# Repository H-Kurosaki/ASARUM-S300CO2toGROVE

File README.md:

# ASARUM-S300CO2toGROVE
ELT社のCO2センサS-300をGroveコネクタに対応させる基板のデータを公開しています。

◯公開しているデータの内容

/main/GerberData

Grove化基板のガーバーデータ、FusionPCBのファイル名に準拠しています。このフォルダの内容をzipに圧縮すればそのまま発注に使えます。

/main/EagleBoard

Eagle形式のPCBデータ(GerberDataの元データ)

/main/EagleLbr

Eagle形式のライブラリS-300のフットプリント。背面のJ11,J12コネクタのみ配置してあります。おまけでK30のフットプリントも入っていますが検証していません。

/main/BOM

実装部品表

/main/ArduinoS300test

Arduino UNO R3を用いた場合のテストプログラム。I2C接続時の読み出し試験。

◯基板の仕様

S-300のI2CインターフェースをGroveケーブルで引き出すことができます。
S-300の裏側の2mmピッチコネクタを使用するので基板から簡単にセンサを着脱できる実装が行えます。
MCDL校正を行う場合は通電して起動後に10分間MCDLと書かれた部分のピンをジャンパーで短絡してください。
その他I2C以外のピンもよく使いそうなものはピンヘッダに出ています。

基板の穴の間隔は未来工業社のウォルボックスWB-DMシリーズなどの穴の位置に合わせてあります。

◯使用上の注意とライセンス

本リポジトリで公開しているデータはELT社の公式なものではありません。
本リポジトリでライセンスを設定可能なファイルにはMITライセンスを適用させていただきます。
二次配布、商用利用も可能なデータとして配布しますが、本データを使用したことによって生じた結果については利用者が全ての責任を負うものとします。

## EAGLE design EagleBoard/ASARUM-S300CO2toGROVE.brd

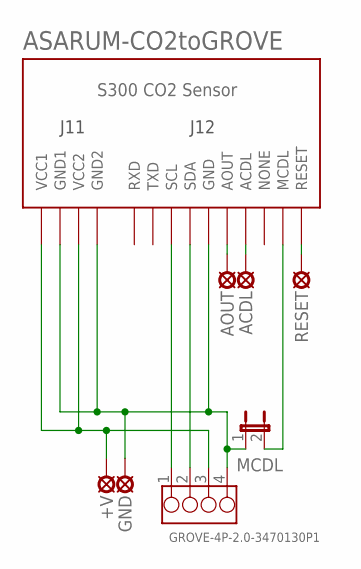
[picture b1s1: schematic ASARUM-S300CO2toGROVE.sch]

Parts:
+V: LSP10
ACDL: LSP10
AOUT: LSP10
GND: LSP10
GROVE_I2C: GROVE-4P-2.0-3470130P1; 4P-2.0
MCDL: JP1E; JP1
RESET: LSP10
S300: S300; S300REV

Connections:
GND: GND.MP, GROVE_I2C.4, MCDL.1, S300.J11P$2_GND (GND1), S300.J11P$4_GND (GND2), S300.J12P$5_GND (GND)
unnamed: GROVE_I2C.1, S300.J12P$3_SCL (SCL)
unnamed: GROVE_I2C.2, S300.J12P$4_SDA (SDA)
unnamed: MCDL.2, S300.J12P$9_MCDL (MCDL)
unnamed: RESET.MP, S300.J12P$10_RESET (RESET)
unnamed: ACDL.MP, S300.J12P$7_ACDL (ACDL)
unnamed: AOUT.MP, S300.J12P$6_AOUT (AOUT)
VCC: +V.MP, GROVE_I2C.3, S300.J11P$1_VCC (VCC1), S300.J11P$3_VCC (VCC2)

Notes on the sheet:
ASARUM-CO2toGROVE

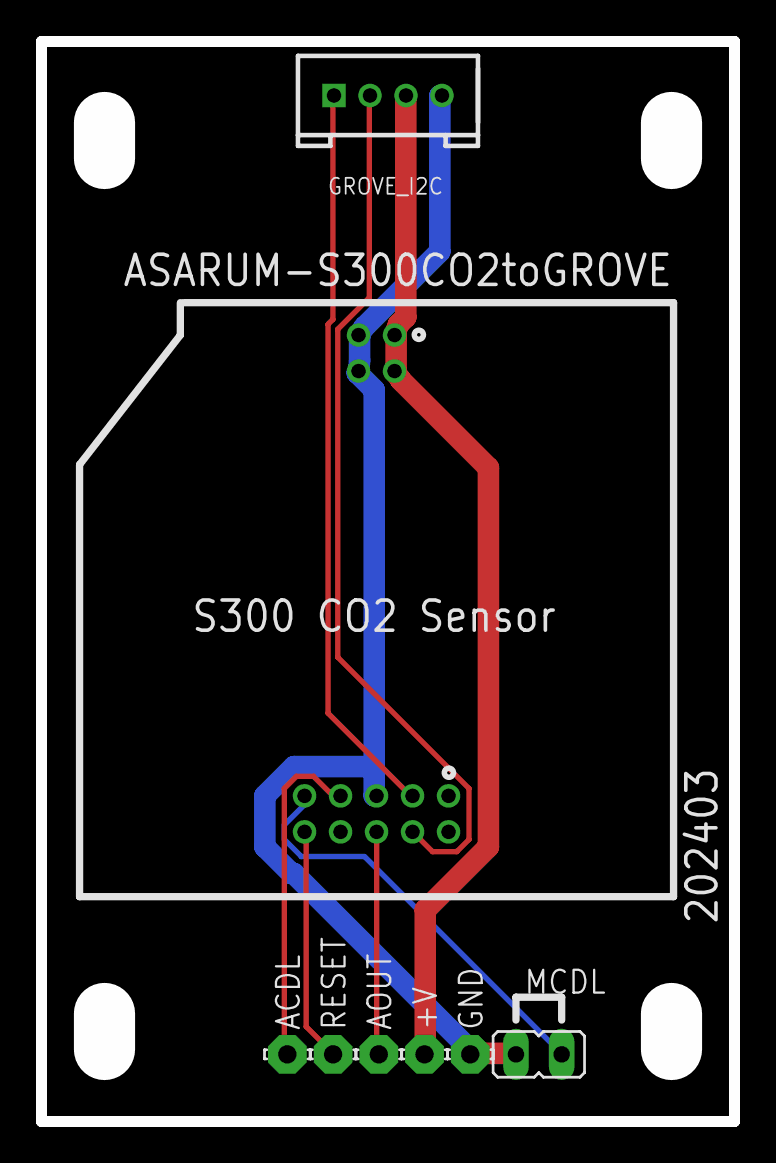
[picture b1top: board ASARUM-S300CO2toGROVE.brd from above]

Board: 2 copper layers, 38.5 x 60.0 mm, 8 parts (0 on the bottom side), 8 nets.

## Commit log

2024-08-08 Rename bom.txt to partslist.txt
